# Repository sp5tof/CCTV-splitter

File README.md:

This project is about switching the composite signals come from 4 CCTV cameras into one video receiver. Switching is done by remote IR controller (f.ex. TV remote controller).
Four IR codes have to be preconfigured within the arduino code.

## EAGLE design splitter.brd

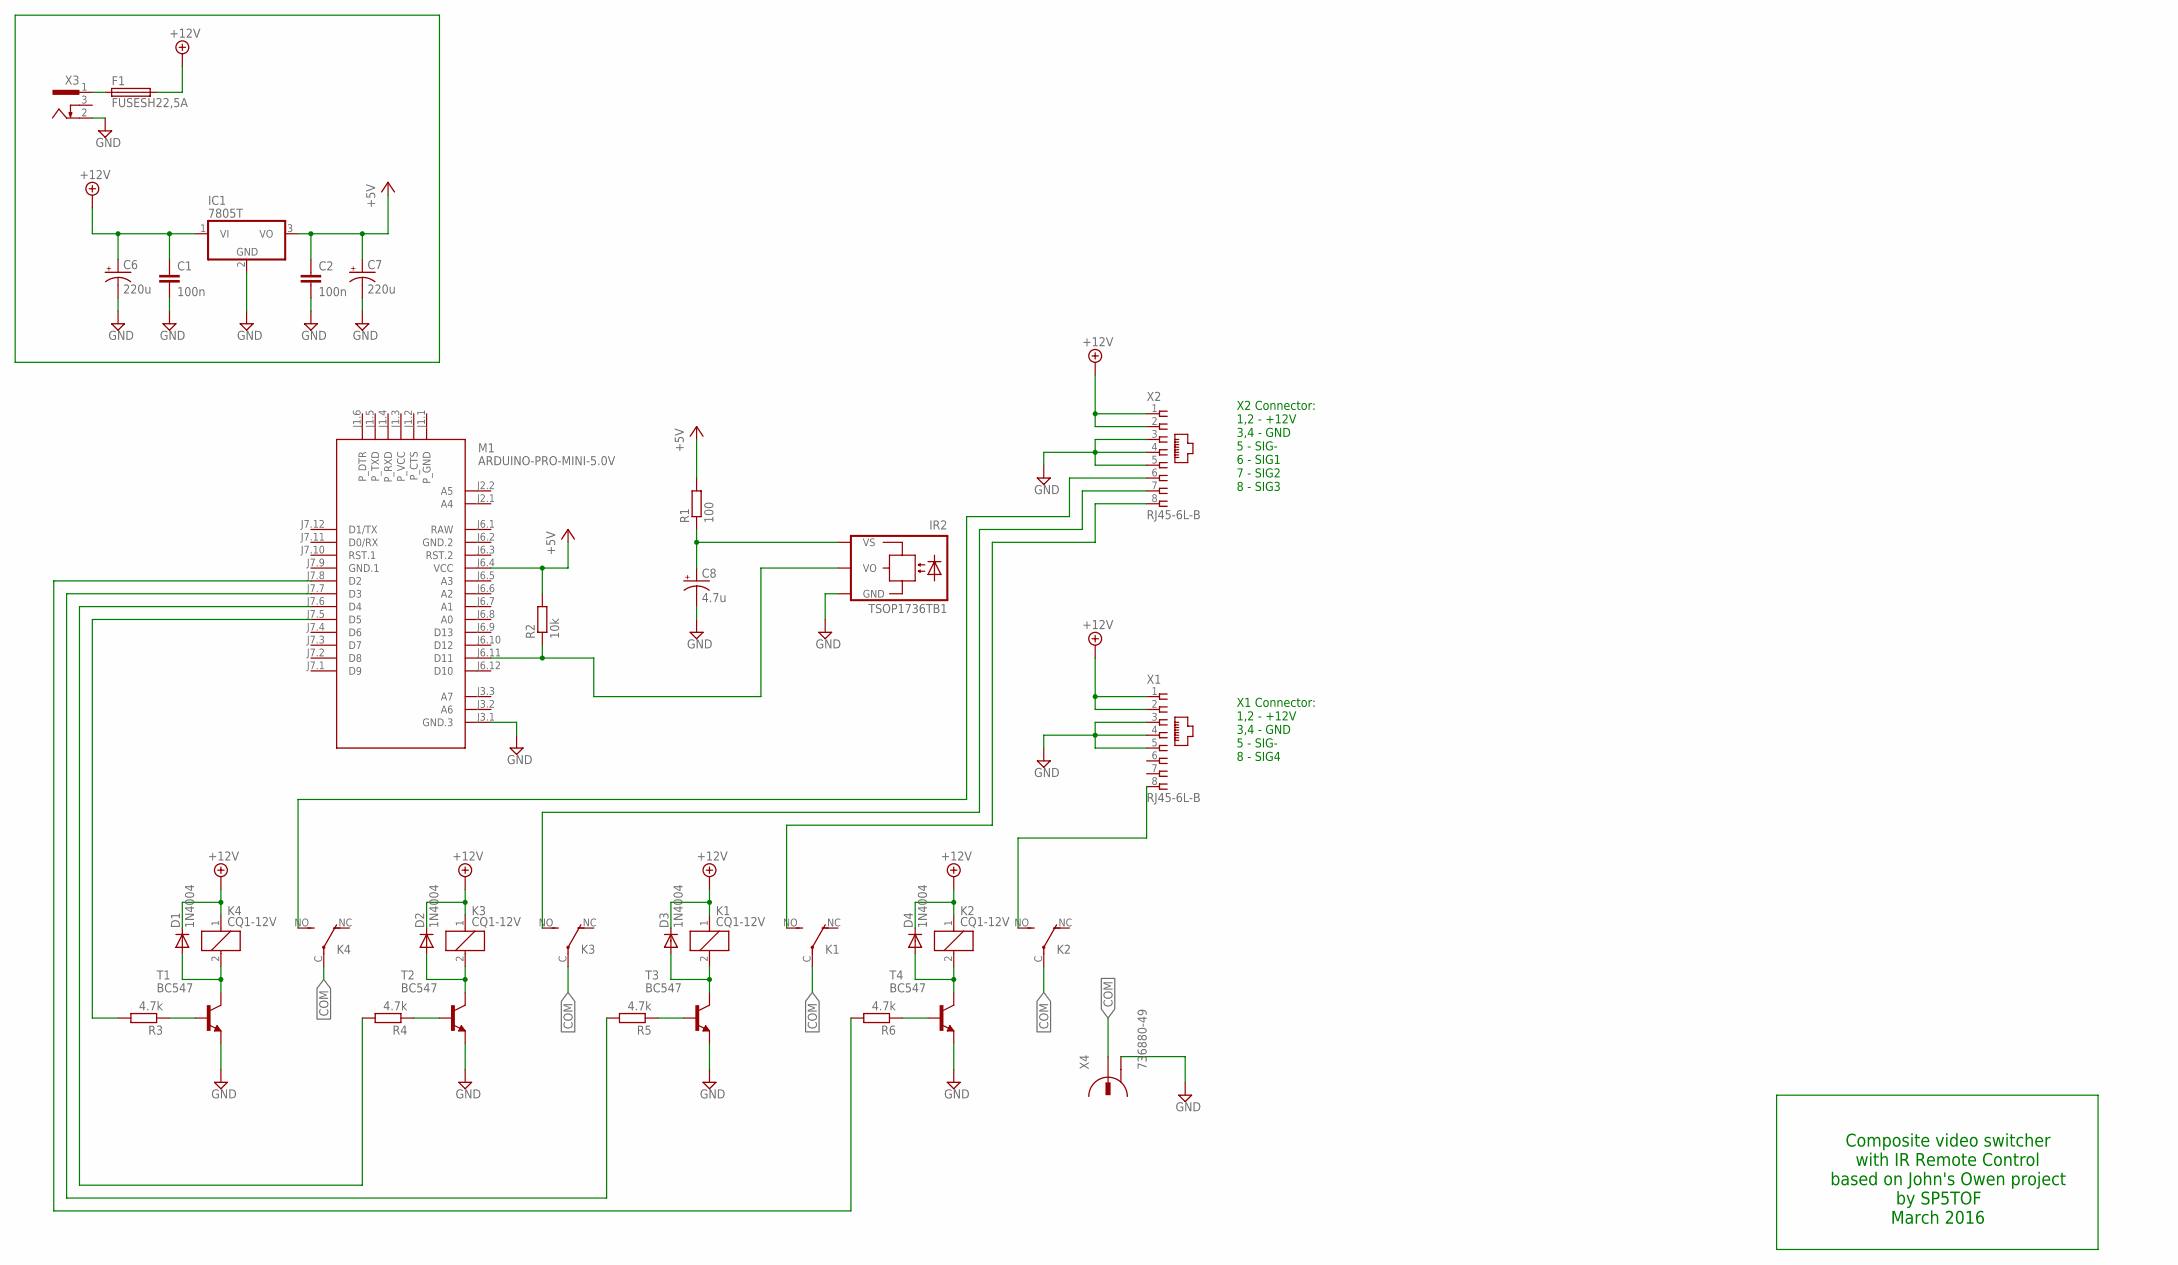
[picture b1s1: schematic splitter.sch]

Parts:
C1, C2: 100n; C025-024X044
C6, C7: 220u; CPOL-RADIAL-10UF-25V
C8: 4.7u; CPOL-RADIAL-10UF-25V
D1, D2, D3, D4: 1N4004; DO41-10
F1: FUSESH22,5A; SH22,5A
IC1: 7805T; TO220H
IR2: TSOP1736TB1; TSOP17_TB1
K1, K2, K3, K4: CQ1-12V; CQ1
M1: ARDUINO-PRO-MINI-5.0V; ARDUINO-PRO-MINI
R1: 100; 0204/7
R2: 10k; 0204/7
R3, R4, R5, R6: 4.7k; 0204/7
T1, T2, T3, T4: BC547; TO92
X1, X2: RJ45-6L-B; RJ45-NO-SHIELD
X3: 733980-62
X4: 736880-49

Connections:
+5V: C2.1, C7.1 (+), IC1.3 (VO), M1.J6.4 (VCC), R1.2, R2.2
+12V: C1.1, C6.1 (+), D1.C, D2.C, D3.C, D4.C, F1.2, IC1.1 (VI), K1.1, K2.1, K3.1, K4.1, X1.1, X1.2, X2.1, X2.2
COM: K1.C, K2.C, K3.C, K4.C, X4.1
GND: C1.2, C2.2, C6.2 (-), C7.2 (-), C8.2 (-), IC1.2 (GND), IR2.GND, M1.J3.1 (GND.3), T1.1 (E), T2.1 (E), T3.1 (E), T4.1 (E), X1.3, X1.4, X1.5, X2.3, X2.4, X2.5, X3.2, X4.2
GND.1: M1.J7.9 (GND.1)
GND.2: M1.J6.2 (GND.2)
unnamed: C8.1 (+), IR2.VS, R1.1
unnamed: F1.1, X3.1
unnamed: IR2.VO, M1.J6.11 (D11), R2.1
unnamed: R3.1, T1.2 (B)
unnamed: R4.1, T2.2 (B)
unnamed: R5.1, T3.2 (B)
unnamed: R6.1, T4.2 (B)
unnamed: D1.A, K4.2, T1.3 (C)
unnamed: M1.J7.7 (D3), R5.2
unnamed: M1.J7.6 (D4), R4.2
unnamed: D2.A, K3.2, T2.3 (C)
unnamed: D3.A, K1.2, T3.3 (C)
unnamed: D4.A, K2.2, T4.3 (C)
unnamed: K4.NO (S), X2.6
unnamed: K3.NO (S), X2.7
unnamed: K1.NO (S), X2.8
unnamed: K2.NO (S), X1.8
unnamed: M1.J7.5 (D5), R3.2
unnamed: M1.J7.8 (D2), R6.2
RAW: M1.J6.1 (RAW)

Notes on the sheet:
X2 Connector: 1,2 - +12V 3,4 - GND 5 - SIG- 6 - SIG1 7 - SIG2 8 - SIG3
X1 Connector: 1,2 - +12V 3,4 - GND 5 - SIG- 8 - SIG4
Composite video switcher with IR Remote Control based on John's Owen project by SP5TOF March 2016

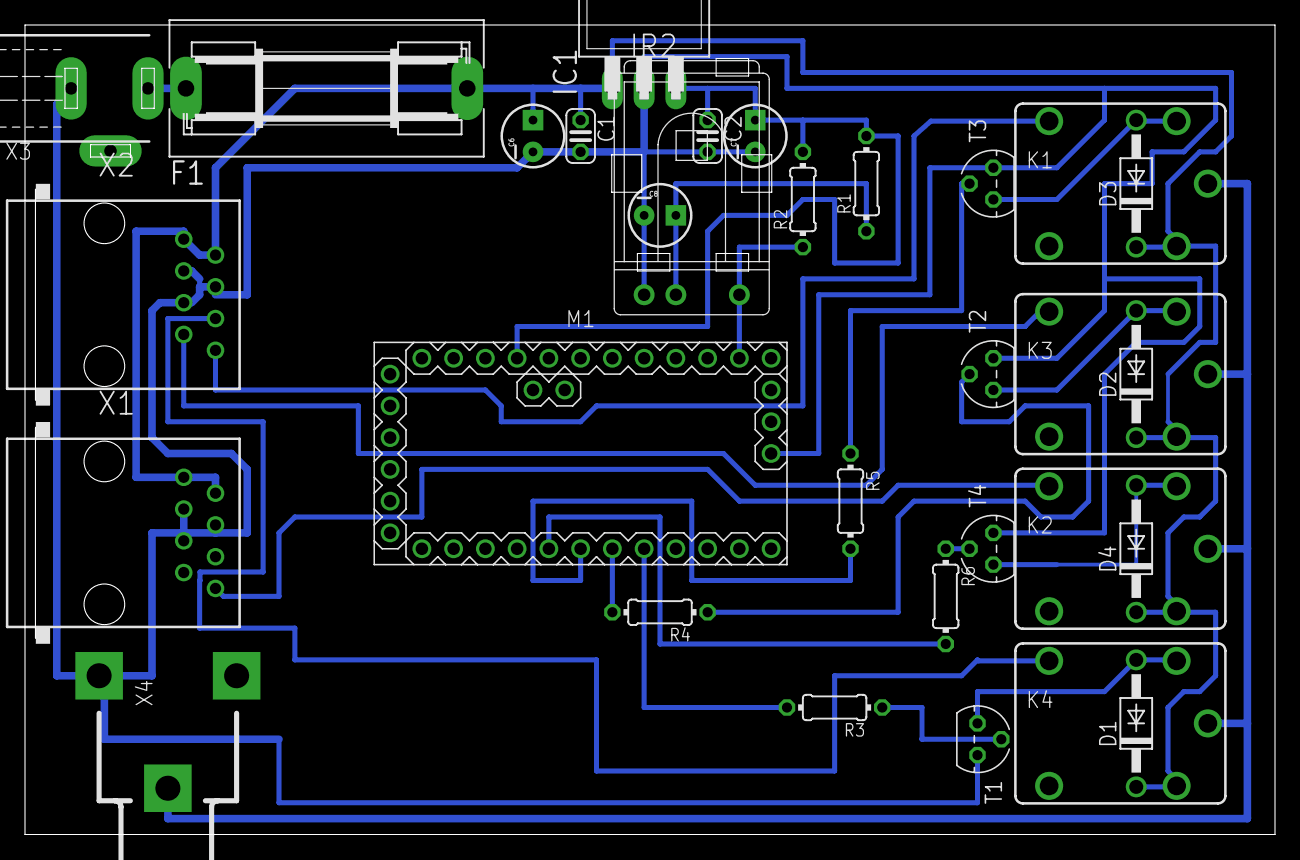
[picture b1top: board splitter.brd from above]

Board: 2 copper layers, 100.0 x 64.8 mm, 31 parts (0 on the bottom side), 23 nets.

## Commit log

2025-01-07 Add files via upload
    Schema
2025-01-07 Add files via upload
    Photo of the circuit.
2025-01-07 Add files via upload
    Arduino code
2025-01-07 Add files via upload
    Eagle board project
2025-01-07 Add files via upload
    Eagle schema

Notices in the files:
parts and their libraries:
diy-modules: Released under the Creative Commons Attribution 4.0 International License: http://creativecommons.org/licenses/by/4.0
